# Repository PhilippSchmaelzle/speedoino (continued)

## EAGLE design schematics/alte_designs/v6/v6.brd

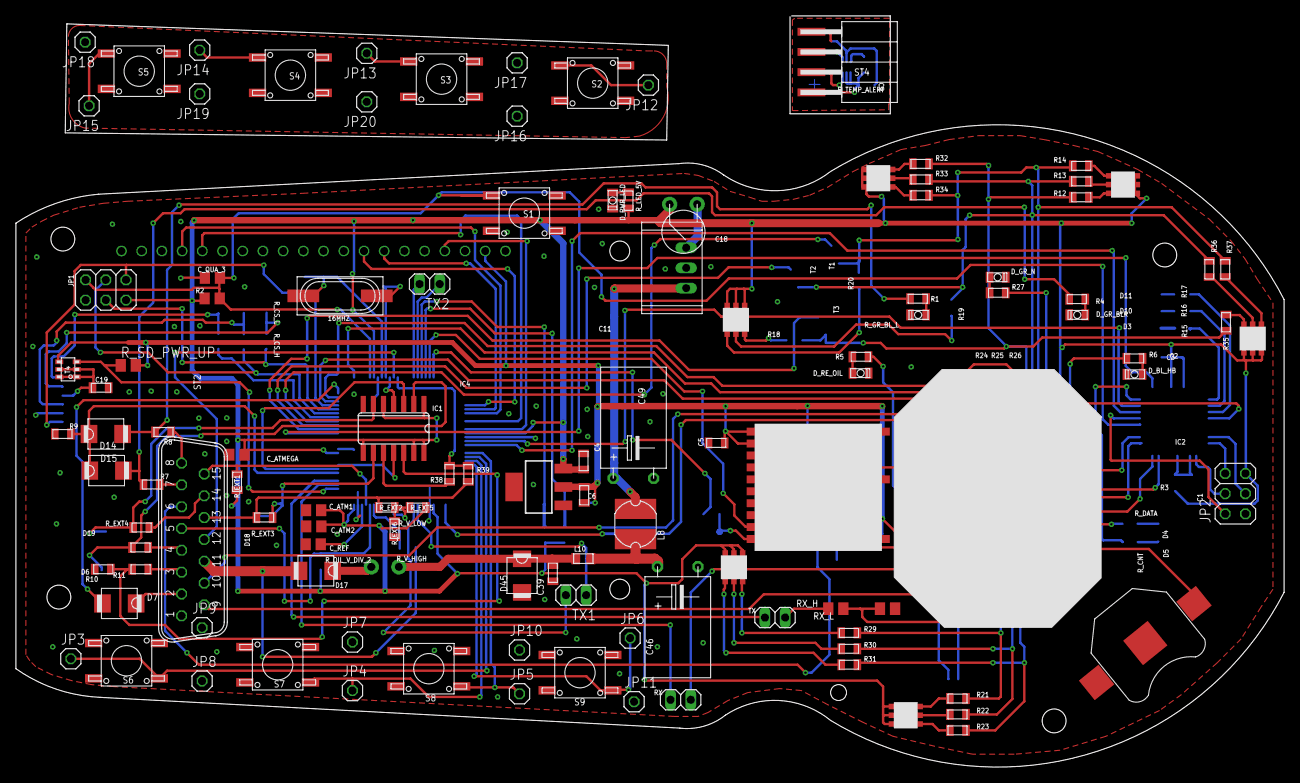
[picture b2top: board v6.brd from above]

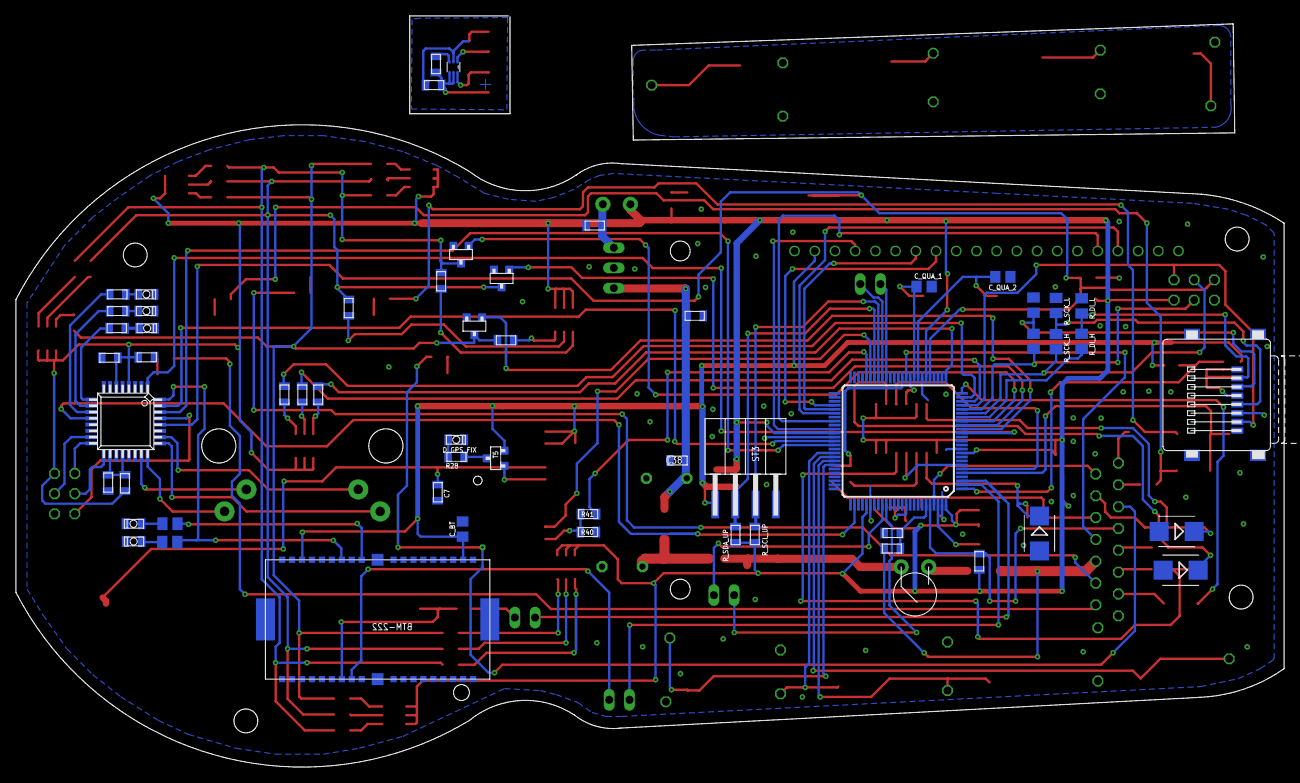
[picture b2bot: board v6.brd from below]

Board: 2 copper layers, 159.4 x 80.7 mm, 174 parts (58 on the bottom side), 146 nets.

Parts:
5V_F: 600mA; POLY_FUSE
12V_F1: 1.1A; POLY_FUSE
16MHZ: 16Mhz; XT-HC49S-SMD
18632422: RGB_LED
BAT_CLIP1: F_908642; BATTCON_12MM
BLUETOOTH: BTM-222
C1, C2, C3, C5, C7, C9: 100nF; 0805
C4, C11, C18: 100n/20V; 0805
C6: 10u/20V; 0805
C19: 100n; 0805
C38, C39: 2µ2/100V; 0805
C46: 470µ; EL-5-8X13R
C49: 470µ; EL-5-8X13
C_ATM1, C_ATM2: 100nF; C0805
C_ATMEGA: 100nF; C0805
C_BT: 200nF; C0805
C_QUA_1, C_QUA_2, C_QUA_3: 22pF; C0805
C_REF: 100nF; C0805
D3, D10, D11: LED-0805
D4: Red; LED-0805
D5: Blue; LED-0805
D6: 20V-Zdiode; SMB
D7, D14, D15, D17: SS24; SMB
D18, D19: 20V-ZD.; SMB
D45: SM6T30V; SMB
DCDC53.3: AP1117E33G; SOT223
D_BL_HB: HighB _ 645-598-8191-107F; LED-0805
D_GPS_FIX: Red; LED-0805
D_GR_BLR: BL_R; LED-0805
D_GR_N: N _ M 645-598-8110-107F; LED-0805
D_PWR_LED: Red; LED-0805
D_RE_OIL: OIL M 645-598-8110-107F; LED-0805
GPS: MT3329
IC1: 4093D; SO14
IC2: AT-MEGA-8; TQFP-32_7X7
IC4: ATMEGA2560-16AU; TQFP100
JP1, JP2: ICSP; 2X03
JP3, JP4, JP5, JP6, JP7, JP8, JP9, JP10, JP11, JP12, JP13, JP14, JP15, JP16, JP17, JP18, JP19, JP20: 1X01
L8: 22µH 1A; L-PD54
L10: BLM21PG221SN1; 0805+603
NHD_2.7: NHD_2.7_SOLO_RO
PWR_R78: R-7805-1.0; SIP3
R1, R4: 250R; 0805
R2: 10K; R0805
R3: 10R; 0805
R5: 565R; 0805
R6: 490R; 0805
R7, R8: 310R; 0805
R9: 10k; 0805
R10: 5k / n.b. (Reed); 0805
R11: 7k; 0805
R12, R18, R21, R24, R29, R32, R35: 100R; 0805
R13, R14, R19, R20, R22, R23, R25, R26, R30, R31, R33, R34, R36, R37: 90R; 0805
R15, R16, R17, R28: 1k; 0805
R27: 560R; 0805
R38: 0R; 0805
R39: n.b.; 0805
R40: 2k7; 0805
R41: 1k2; 0805
RX: 1X02
RX_H: 1k2; M0805
RX_L: 2k7; M0805
R_CNT: 220R; M0805
R_CS_H: 1k2; M0805
R_CS_L: 2k7; M0805
R_DATA: 220R; M0805
R_DI_H: 1k2; M0805
R_DI_L: 2k7; M0805
R_DZ_DIV1: 5k; 0805
R_EXT1: 390R; 0805
R_EXT2, R_EXT5, R_EXT6: n.b.; 0805
R_EXT3, R_EXT4: 5k; 0805
R_GR_BL_L: BL_L; LED-0805
R_LED_5V: 1k; 0805
R_OIL_V_DIV_2: 220; 0805
R_SCK_H: 1k2; M0805
R_SCK_L: 2k7; M0805
R_SCL_UP: 1K; 0805
R_SDA_UP: 1K; 0805
R_SD_PWR_UP: 10k; M0805
R_TEMP_ALERT: 1k; 0805
R_V_HIGH: 2k2; 0805
R_V_LOW: 1k; 0805
S1: SW-ECO
S2, S6: U; SW-ECO
S3, S7: R; SW-ECO
S4, S8: D; SW-ECO
S5, S9: L; SW-ECO
ST2: SD_MICRO
ST3, ST4: BL17SMD_1X4
T1, T2, T3, T5: Farnell: 1299313; SOT-23
T4: T-IRLMS6702; SOT-23-6
TMP102AIDRLT: TMP102; SOT563
TX, TX1, TX2: 1X02
U$3: STEPPER
U$14, U$15, U$16, U$18, U$19, U$20: RGB_LED
X2: IP67-SUB-D

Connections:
12V: D17.A, R_V_HIGH.1, X2.11
12V_SAFE: 12V_F1.P$2, C39.1, D45.K, L10.1
+3V3_EXT: BLUETOOTH.P$2, BLUETOOTH.P$17, C5.2, C6.2, C_BT.1, DCDC53.3.2, GPS.EN, GPS.VCC, NHD_2.7.VDD0, R_SD_PWR_UP.2, ST3.1, T4.4, T5.2
+3V3_EXT_S: C19.2, ST2.4, T4.1, T4.2, T4.5, T4.6
A0: IC4.97, R_EXT1.1, X2.15
A1: IC4.96, R_OIL_V_DIV_2.1, X2.5
A2: IC4.95, R_V_HIGH.2, R_V_LOW.1
A7: IC4.90, R_EXT2.2, R_EXT5.1, R_EXT6.1
A12: IC4.85, TX1.2
A13: IC4.84, TX1.1
ARD_RES_OUT: C_QUA_3.1, IC2.28, IC4.30, JP1.2, R2.1, S1.4
ARD_RX_5: RX_H.1, TX.1
ARD_RX_33: BLUETOOTH.P$26, RX_H.2, RX_L.2
BAT+: C11.1, C38.2, C49.1, L8.2, PWR_R78.IN
BLUE_INSTR: R14.2, R20.2, R23.2, R31.2, R34.2, R37.2, T1.3
BL_L: R8.1, X2.8
BL_R: R7.1, X2.7
B_D: IC4.66, JP5.1, S8.4
B_L: IC4.69, JP6.1, S9.4
B_R: IC4.68, JP4.1, S7.4
B_U: IC4.67, JP3.1, S6.4
CONNECT: BLUETOOTH.P$13, IC2.32, R_CNT.2
D2: IC1.3, IC4.6
D3: IC1.11, IC4.7
D4: IC4.1, R_SD_PWR_UP.1, T4.3
D5: D14.K, D15.K, IC4.5, R9.2
D6: IC2.1, IC4.15
D7: IC4.16, T3.1
D8: IC4.17, T2.1
D9: IC4.18, T1.1
D10: IC4.23, R25.2
D11: IC4.24, R26.2
D12: D7.A, IC4.25
D13: IC4.26, R24.2
D20: IC4.44, R_SDA_UP.2, ST3.2
D21: IC4.43, R_SCL_UP.2, ST3.3
D23: IC2.12, IC4.77
D30: IC4.60, NHD_2.7.DC
D32: IC4.58, NHD_2.7.RES
D34: IC4.56, NHD_2.7.CS
D35: IC4.55, NHD_2.7.SCLK
D36: IC4.54, NHD_2.7.SDIN
D42: IC4.42, TX2.1
D43: IC4.41, TX2.2
D47: IC4.37, R38.2, R39.2
D48: IC4.36, X2.12
D49: IC1.4, IC4.35
D50: IC4.22, JP1.6, ST2.7
D51: IC4.21, JP1.3, R_CS_H.2
D52: IC4.20, JP1.4, R_SCK_H.2
D53: IC4.19, R_DI_H.2
DZ: D6.C, IC1.2, R_DZ_DIV1.2
DZ_IN: R_DZ_DIV1.1, X2.4
EXTEND1: D19.C, IC1.6, R_EXT4.2
EXTEND2: D18.C, IC1.9, R_EXT3.2
EXT_3.3V: C9.1, R_TEMP_ALERT.2, ST4.4, TMP102AIDRLT.4, TMP102AIDRLT.5
EXT_GND: C9.2, ST4.1, TMP102AIDRLT.2
EXT_SCL: ST4.2, TMP102AIDRLT.1
EXT_SDA: ST4.3, TMP102AIDRLT.6
E_B_D: JP14.1, S4.4
E_B_L: JP15.1, S5.4
E_B_R: JP13.1, S3.4
E_B_U: JP12.1, S2.4
E_GND: JP16.1, JP17.1, JP18.1, JP19.1, JP20.1, S2.1, S3.1, S4.1, S5.1
GND: BAT_CLIP1.GND, BLUETOOTH.P$1, BLUETOOTH.P$10, BLUETOOTH.P$18, BLUETOOTH.P$19, BLUETOOTH.P$29, BLUETOOTH.P$38, BLUETOOTH.P$AGND, BLUETOOTH.P$BGND, C1.2, C2.1, C3.1, C4.1, C5.1, C6.1, C7.2, C11.2, C18.2, C19.1, C38.1, C39.2, C46.2, C49.2, C_ATM1.2, C_ATM2.2, C_ATMEGA.2, C_BT.2, C_QUA_1.1, C_QUA_2.1, C_QUA_3.2, C_REF.2, D3.2, D4.2, D5.2, D6.A, D10.2, D11.2, D18.A, D19.A, D45.A, DCDC53.3.1, D_BL_HB.2, D_GPS_FIX.2, D_GR_BLR.2, D_GR_N.2, D_PWR_LED.2, D_RE_OIL.2, GPS.GND, GPS.GND2, GPS.GND_3, GPS.GND_4, GPS.GND_5, IC1.7, IC2.3, IC2.5, IC2.21, IC4.11, IC4.32, IC4.62, IC4.81, IC4.99, JP1.1, JP2.1, JP7.1, JP8.1, JP9.1, JP10.1, JP11.1, NHD_2.7.GND0, NHD_2.7.GND1, NHD_2.7.GND2, NHD_2.7.GND3, NHD_2.7.GND4, NHD_2.7.GND5, NHD_2.7.GND6, NHD_2.7.GND7, NHD_2.7.GND8, NHD_2.7.GND9, PWR_R78.GND, R9.1, R10.2, R40.2, RX_L.1, R_CS_L.1, R_DI_L.1, R_EXT6.2, R_GR_BL_L.2, R_SCK_L.1, R_V_LOW.2, S1.1, S6.1, S7.1, S8.1, S9.1, ST2.6, ST2.GND, ST2.GND2, ST2.GND3, ST2.GND4, ST3.4, T1.2, T2.2, T3.2, X2.1
GREEN_INSTR: R13.2, R19.2, R22.2, R30.2, R33.2, R36.2, T2.3
HIGH_BEAM: R6.1, X2.9
KUPPLUNG_IN: D7.K, X2.2
M1: IC2.23, U$3.1+
M2: IC2.24, U$3.1-
M3: IC2.25, U$3.2+
M4: IC2.26, U$3.2-
MISO_AT8: IC2.16, JP2.6
MOSI_AT8: IC2.15, JP2.3
unnamed: C46.1, L8.1, L10.2
unnamed: D14.A, R1.1, R8.2
unnamed: C1.1, IC2.18, IC2.20, R3.2
unnamed: R_TEMP_ALERT.1, TMP102AIDRLT.3
unnamed: D5.1, R_CNT.1
unnamed: R31.1, U$18.B-
unnamed: R30.1, U$18.G-
unnamed: R29.1, U$18.R-
unnamed: D_PWR_LED.1, R_LED_5V.2
unnamed: R34.1, U$16.B-
unnamed: D15.A, R4.1, R7.2
unnamed: D4.1, R_DATA.1
unnamed: R_CS_H.1, R_CS_L.2, ST2.3
unnamed: IC2.11, R17.1
unnamed: D_GPS_FIX.1, R28.2
unnamed: GPS.3D-FIX, T5.1
unnamed: R28.1, T5.3
unnamed: IC2.10, R16.1
unnamed: 5V_F.P$1, C18.1, PWR_R78.OUT
unnamed: IC2.9, R15.1
unnamed: R33.1, U$16.G-
unnamed: R32.1, U$16.R-
unnamed: R_SCK_H.1, R_SCK_L.2, ST2.5
unnamed: 12V_F1.P$1, D17.K
unnamed: R_DI_H.1, R_DI_L.2, ST2.2
unnamed: R37.1, U$14.B-
unnamed: R36.1, U$14.G-
unnamed: R35.1, U$14.R-
unnamed: R1.2, R_GR_BL_L.1
unnamed: D_GR_BLR.1, R4.2
unnamed: 16MHZ.2, C_QUA_2.2, IC4.33
unnamed: 16MHZ.1, C_QUA_1.2, IC4.34
unnamed: C_REF.1, IC4.98
unnamed: D_RE_OIL.1, R5.2
unnamed: D_BL_HB.1, R6.2
unnamed: IC1.10, R38.1
unnamed: R12.1, U$15.R-
unnamed: R13.1, U$15.G-
unnamed: R14.1, U$15.B-
unnamed: 18632422.R-, R18.1
unnamed: 18632422.G-, R19.1
unnamed: 18632422.B-, R20.1
unnamed: R21.1, U$19.R-
unnamed: R22.1, U$19.G-
unnamed: R23.1, U$19.B-
unnamed: R24.1, U$20.R-
unnamed: R25.1, U$20.G-
unnamed: R26.1, U$20.B-
unnamed: D_GR_N.1, R27.2
unnamed: R_EXT4.1, X2.14
unnamed: R39.1, R_EXT2.1, R_EXT3.1, X2.13
N_IN: R27.1, X2.10
OIL_PRESSURE: R5.1, X2.6
P0: D3.1, R15.2
P1: D10.1, R16.2
P2: D11.1, R17.2
RED_INSTR: R12.2, R18.2, R21.2, R29.2, R32.2, R35.2, T3.3
REED: IC1.12, R10.1, R11.2
REED_IN: R11.1, X2.3
RESETAVR_AT8: IC2.29, JP2.2
RX0: IC4.2, RX.1
RX1: GPS.TXD, IC4.45
RX3: IC2.31, IC4.63
SCK_AT8: IC2.17, JP2.4
TO_DATA_LED: BLUETOOTH.P$11, R_DATA.2
TX: BLUETOOTH.P$27, RX.2
TX0: IC4.3, TX.2
TX1: IC4.46, R41.2
TX1_3.3: GPS.RXD, R40.1, R41.1
TX3: IC2.30, IC4.64
VDD: 5V_F.P$2, 18632422.B+, 18632422.G+, 18632422.R+, C2.2, C3.2, C4.2, C_ATM1.1, C_ATM2.1, C_ATMEGA.1, DCDC53.3.3, IC1.1, IC1.5, IC1.8, IC1.13, IC1.14, IC2.4, IC2.6, IC4.10, IC4.31, IC4.61, IC4.80, IC4.100, JP1.5, JP2.5, R2.2, R3.1, R_EXT1.2, R_EXT5.2, R_LED_5V.1, R_OIL_V_DIV_2.2, R_SCL_UP.1, R_SDA_UP.1, U$14.B+, U$14.G+, U$14.R+, U$15.B+, U$15.G+, U$15.R+, U$16.B+, U$16.G+, U$16.R+, U$18.B+, U$18.G+, U$18.R+, U$19.B+, U$19.G+, U$19.R+, U$20.B+, U$20.G+, U$20.R+
V_BAK: BAT_CLIP1.PWR@1, C7.1, GPS.VBACKUP

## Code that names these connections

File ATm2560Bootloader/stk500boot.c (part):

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//************************************************************************
// init display
static void init_display(void){
	DDRC = 0x00 | (1<<PC7) | (1<<PC5) | (1<<PC3) | (1<<PC2) | (1<<PC1);

	_delay_ms(1); // TODO: Change to 1 ?

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	unsigned int	boot_state;

	/////////Kolja von hier/////////
	/* enabled in ph3 to read if its a bluetooth reset*/
	DDRH  &= ~(1<<PH3); // one input
	PORTH =  0x00 | (1<<PH3); // with pullup

	/* enabled pull up on CAN CS connection, to deactivate can bus interface (interface is low active)*/
	PORTK |= (1<<PK4);
	/////////Kolja bis hier/////////


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
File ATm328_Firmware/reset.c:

#include <avr/io.h>
//#include <avr/iom328p.h>
#include <avr/interrupt.h>
#include <util/delay.h>
#include <stdlib.h>
#include <stdio.h>
#include <stdint.h>
#include "global.h"
#include "reset.h"
int ledstate=0;

void reset_init(){
	// IO konfigurieren - LED's
	//DDRD 0=eingang, 1=ausgang
	//PORTD 1=pullup 0=kein pullup
	DDRD = 0x00 |(1<<PD5) |(1<<PD6) |(1<<PD7); // 3x led AUSGANG,
	PORTD = 0x00 |(1<<PD2) | (1<<PD3); // kein Pull up, außer an den interrupt eingängen
	//0xFF & ~((1<<PD7) | (1<<PD6) | (1<<PD5) | (1<<PD3)); // alle LEDs an, alle einguenge auf pullup bis auf D3, 20 - 50 kR => 0.1 - 0.25 mA

	// interrupts aktivieren
	EICRA |= (1<<ISC00) | (1<<ISC10);           //jede Flanke von INT0 oder INT1 als auslueser
	EICRA &= ~((1<<ISC01) | (1<<ISC11));        //jede Flanke von INT0 oder INT1 als auslueser
	EIMSK  |= (1<<INT0) | (1<<INT1);			//Global Interrupt Flag fuer INT0 und INT1

	counter_bt=0;
	counter_avr=0;
	reset_led=0; // damit die am anfang etwas leuchtet, show ...
	reset_bt_running=0; // 1=bt reset am laufen, 0=nix
	reset_avr_running=0;// 1=avr reset am laufen, 0=nix
	reset_global_active=1; // 1 = active, 0 = inactive
	last_avr_state=0; // 1=letzte flanke war steigend,0=fallend
	last_bt_state=0;  // 1=letzte flanke war steigend,0=fallend
	last_rst=0;
	counter_bt_init=0; // zählt die pulse am anfang um nicht zu früh ein reset auszulösen wenn die jeweiligen quellen noch starten
}

// funktion zum ruecksetzen und eventuellen verweilen (spezial_down=1) im bootloader
void reset(int spezial_down){
	if(reset_global_active){
		/* Vorgehen:
		 * 1. Interrupts aus
		 * 2. Reset starten
		 * 3. Spezialleitung auf LOW
		 * 4. LED AN
		 * 5. Warten
		 * 6. Reset wieder zurueckschalten
		 * 7. LED wider aus
		 * 8. Spezialleitung wieder zurueck als input
		 */
		// 1. interrupts aus
		cli();

		// 2. Pin c5 auf Ausgang und auf LOW ziehen
		DDRC  |=  (1<<PC5); // pc5 auf ausgang ( reset )
		PORTC &= ~(1 << RST_PIN); // reset auf low

		// 3. spezialleitung auf masse ziehen
		if(spezial_down==1){
			DDRD |= (1<<PD3); // pd3 auf ausgang
			PORTD &= ~(1<<PD3); // pd3 auf low
		}

		// 4. LED an
		if(DEBUG_LEDS){
			PORTD |= (1 << RST_LED);// led an
		}

		// 5. Warten
		_delay_ms(200);

		// 6.
		DDRC   &= ~(1<<PC5) ; // Reset ausgang wieder auf zuhoeren schalten
		PORTC  |= 1<<PC5; // und ihm ein pull up geben

		// 7. eventuell mehr warten, dann aber zurueck als input
		if(spezial_down==1){
			_delay_ms(10); // extrazeit im bootloader
			PORTD |= (1<<PD3); //<< PD3 bt-flash-spezial-pin auf HIGH ( wie pull up auch )
			DDRD &= ~(1<<PD3); // PD3 wieder auf eingang setzen
		}

		// 8. LED aus
		if(DEBUG_LEDS){
			PORTD &= ~(1 << RST_LED); // led aus
		}

		sei(); // aktiviere interrupts
	}
	counter_avr=0;
	counter_bt=0;
	reset_avr_running=0; // macht das hier sinn? bluetooth sollte hier nicht zurueck gesetzt werden
	// bluetooth macht hier den reset und erst wenn es blinkt dann gibt er ihn frei,
};

void config_timer0(){
	// Timer/Counter 0 prescaler 64 => 8Mhz 127khz
	TIMSK0 = (1<<TOIE0);   //Enable a timer overflow interrupt
	TCCR0A = 0;         //just a normal overflow
	TCCR0B = (1<<CS01) | (1<<CS00);   //count
}

/* overflow vom timer 0 ..
 * prescale 64, cpu_freq=16mhz => 64/16.000.000 = 0,000004sec each increment
 * Timer0 is a 8-Bit Timer => 2⁸=256 Counts to overflow = 0,000004sec*256=0,002048 sec= 1,024 ms
 * Bluetooth pin is: 312ms high,312ms low, we have an interrupt on pin change so we can reset after (312/1,024)*1,2 where 20% is safety
 * 364 Timer overruns is max
 *
 * AVR: Lets say 20sec, 20/0,002=10000 Overruns
 */

ISR(TIMER0_OVF_vect){
	TCNT0=0;   //reset the counter
	if(reset_global_active){//wenn es high ist soll resetet werden
		if(counter_bt>=364 && !reset_bt_running && counter_bt_init>10){ //
			reset_bt_running=1;
			reset(1);
			last_rst=2;
		}

		if(counter_avr>=10000 && !reset_avr_running){
			reset_avr_running=1;
			reset(1); // run reset ohne langen bootloader quatsch
			last_rst=1;
		}

		// nur hochzuehlen wenn auch wirklich kein reset gerade am laufen ist, wir wollen ja kein reset beim flashen
		if(reset_bt_running==0 && reset_avr_running==0){
			counter_bt++;
			counter_avr++;
		};

	};
};


// interrupt handle fuer pin-pd2, hier huengt der BT empfuenger dran
// reagiert auf jede Flanke
ISR(INT0_vect){
	if(counter_bt_init<=10) counter_bt_init++;
	if(bit_is_clear(PIND,2) && last_bt_state){ //wenn der pin low und die var high
		// hier kuennte man die Zeit ausgebena#
		if(DEBUG_LEDS){
			PORTD &= ~(1 << BT_LED); // led aus
		}
		last_bt_state=0;
		counter_bt=0;
		if(reset_bt_running==1){ // if there was an reset, it is done by now
			reset_bt_running=0;
		}
	} else if(bit_is_set(PIND,2) && !last_bt_state) { // wenn der pin high und wir vorher low waren
		if(DEBUG_LEDS){
			PORTD |= (1 << BT_LED);// led an
		}
		last_bt_state=1;
		counter_bt=0;
		if(reset_bt_running==1){ // if there was an reset, it is done by now
			reset_bt_running=0;
		}
	}
}



// interrupt handle fuer pin-pd2, hier huengt der AVR dran
// reagiert auf fallende Flanke, hier die LED AN machen und den zuehler resetten
ISR(INT1_vect){
	/* das ist total geil mit dem last_avr_state: wenn der avr sich programmbedingt aufhuengt
	 * ist sagen wir mal der pin low, dann wird das hier ausgefuehrt, danach lueuft der puffer ueber,
	 * der AVR startet aber nicht durch, last_avr_state=0 && bit_stays_clear zumindest wird der huengende
	 * avr nicht zyklisch an dem Pin wackeln und dadurch wird der reset nicht freigegeben und ein
	 * langsam startendes device bleibt nicht in einer resetschleife huengen, TOP ;)
	 */
	if(bit_is_clear(PIND,3) && last_avr_state){ // fallende flanke, sollte also low sein
		if(DEBUG_LEDS){
			PORTD |= (1 << AVR_LED);// led an
		}
		last_avr_state=0;
	} else if(bit_is_set(PIND,3) && !last_avr_state) { // wenn der pin high und wir vorher low waren
		if(DEBUG_LEDS){
			PORTD &= ~(1 << AVR_LED); // led aus
		}
		last_avr_state=1;
	}
	counter_avr=0;
	reset_avr_running=0;
}

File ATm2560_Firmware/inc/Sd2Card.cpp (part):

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}
//------------------------------------------------------------------------------
void Sd2Card::chipSelectHigh(void) {
	PORTB|=(1<<PB0); //digitalWrite(chipSelectPin_, HIGH);
}
//------------------------------------------------------------------------------
void Sd2Card::chipSelectLow(void) {
	PORTB&=~(1<<PB0); //digitalWrite(chipSelectPin_, LOW);
}
//------------------------------------------------------------------------------
/** Erase a range of blocks.
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	uint32_t arg;

	// set pin modes
	DDRB|=(1<<PB0);//pinMode(chipSelectPin_, OUTPUT);
	chipSelectHigh();
	DDRB&=~(1<<PB3);//pinMode(SPI_MISO_PIN, INPUT);
	DDRB|=(1<<PB2);//pinMode(SPI_MOSI_PIN, OUTPUT);
	DDRB|=(1<<PB1);//pinMode(SPI_SCK_PIN, OUTPUT);

#ifndef SOFTWARE_SPI
	// SS must be in output mode even it is not chip select
	//pinMode(SS_PIN, OUTPUT);
	DDRB|=(1<<PB0);
	// Enable SPI, Master, clock rate f_osc/128 init the chip .. low speed
	SPCR = (1 << SPE) | (1 << MSTR) | (1 << SPR1) | (1 << SPR0);
	// clear double speed
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
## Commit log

2020-05-02 Initial Commit Based on Kolja Windler

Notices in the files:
ATm2560Bootloader/stk500boot.c:
License: GNU General Public License
LICENSE:
Copyright (C) 2006 Peter Fleury
ATm2560_Firmware/inc/Sd2Card.cpp:
Copyright (C) 2009 by William Greiman
This Library is free software: you can redistribute it and/or modify
it under the terms of the GNU General Public License as published by
the Free Software Foundation, either version 3 of the License, or
(at your option) any later version.
